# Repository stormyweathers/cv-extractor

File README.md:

# CV Extractor

This is an envelope detector eurorack module.
It is intended to take in eurorack signals or audio input and output the envelope.

## Description of schematic
An input waveform passes through an adjustable gain noninverting amplifier, then an active rectifier, then finally a 2-pole sallen-key LPF with adjustable gain and cutoff.

## Features

    * Buffered input/output
    * Adjustable input/output gain
    * Adjustable timescale of envelope detection

## Rack info

    * +12V: ?? mA
    * -12V: ?? mA
    *  +5V: unused
    * Width: 8HP   

## Issues

The module works, but its not that great.

    * Gain Pots are oriented reverse, unintuitive
    * Turning the cutoff knob can cause it to oscillate
    * The gain range is too large

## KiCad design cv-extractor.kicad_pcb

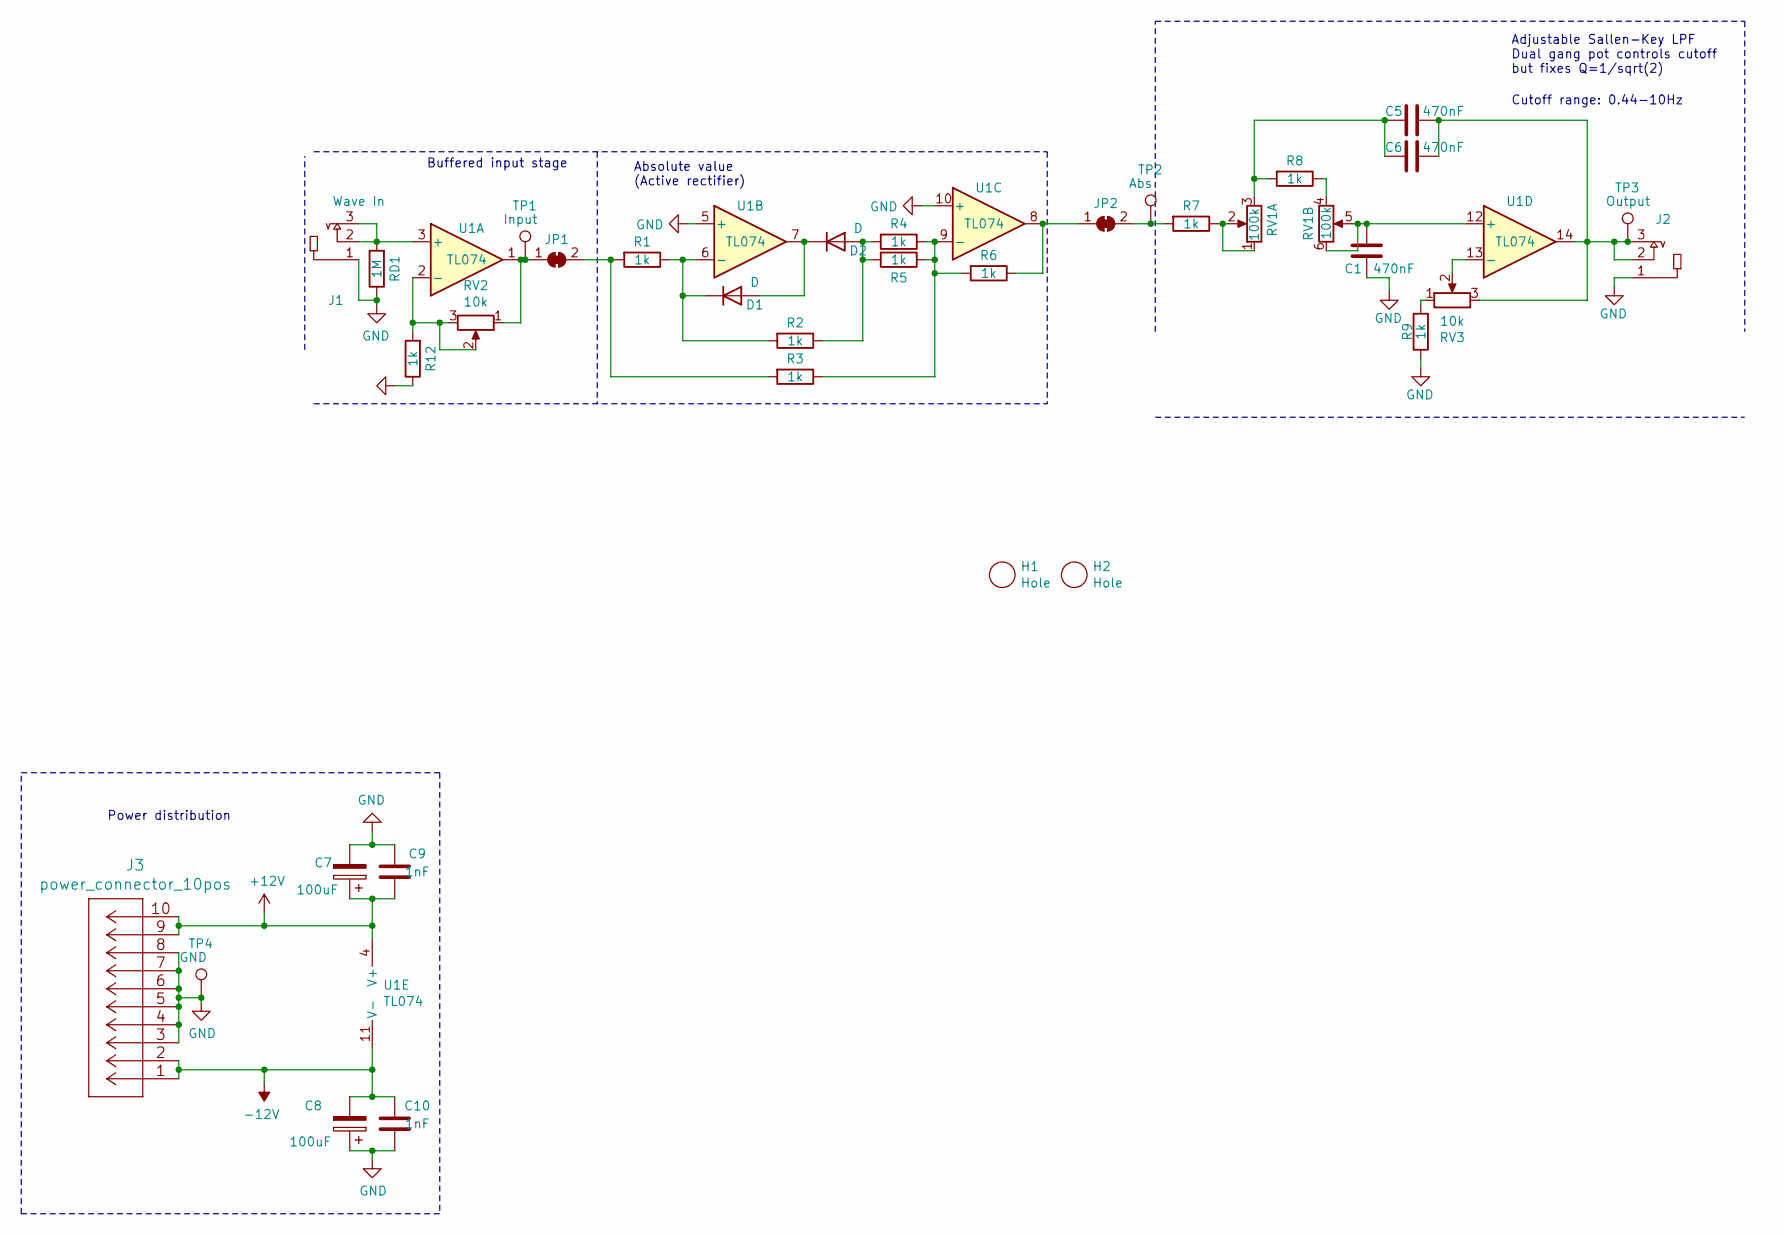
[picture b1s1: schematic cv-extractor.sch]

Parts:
C1, C5, C6: 470nF; C_0603_1608Metric; JLCPCB C1623
C7, C8: 100uF; CP_Elec_6.3x7.7; JLCPCB C176675
C9, C10: 1nF; C_0603_1608Metric; JLCPCB C1588
D1, D2: D; D_SOD-323F; JLCPCB C2128
H1, H2: Hole; MountingHole_3.2mm_M3
J1: Wave In; mono-jack-thonk
J2: CV Out; mono-jack-thonk
J3: power_connector_10pos; Digikey 732-2094-ND
JP1, JP2: SolderJumper_2_Bridged; SolderJumper-2_P1.3mm_Open_RoundedPad1.0x1.5mm
R1, R2, R3, R4, R5, R6, R7, R8, R9, R12: 1k; R_0603_1608Metric; JLCPCB C21190
RD1: 1M; R_0603_1608Metric; JLCPCB C21190
RV1: 100k; dual-pot-P120
RV2, RV3: 10k; pot_bourns_PTV09
TP1: Input; TestPoint_TP107
TP2: Abs; TestPoint_TP107
TP3: Output; TestPoint_TP107
TP4: GND; TestPoint_TP107
U1: TL074; SOIC-14_3.9x8.7mm_P1.27mm

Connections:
+12V: C7.1, C9.2, J3.9, J3.10, U1.4 (V+)
-12V: C8.2, C10.1, J3.1, J3.2, U1.11 (V-)
GND: C1.1, C7.2, C8.1, C9.1, C10.2, J1.1, J2.1, J3.3, J3.4, J3.5, J3.6, J3.7, J3.8, R9.1, R12.1, RD1.1, TP4.1, U1.5 (+), U1.10 (+)
unnamed: C1.2, RV1.5, RV1.6, U1.12 (+)
unnamed: C5.1, C6.1, R8.2, RV1.3
unnamed: C5.2, C6.2, J2.2, J2.3, RV3.3, TP3.1, U1.14
unnamed: D1.1 (K), R1.1, R2.2, U1.6 (-)
unnamed: D1.2 (A), D2.1 (K), U1.7
unnamed: D2.2 (A), R2.1, R4.2, R5.2
unnamed: J1.2, J1.3, RD1.2, U1.3 (+)
unnamed: JP1.1 (A), RV2.1, TP1.1, U1.1
unnamed: JP1.2 (B), R1.2, R3.2
unnamed: JP2.1 (A), R6.1, U1.8
unnamed: JP2.2 (B), R7.2, TP2.1
unnamed: R3.1, R4.1, R5.1, R6.2, U1.9 (-)
unnamed: R7.1, RV1.1, RV1.2
unnamed: R8.1, RV1.4
unnamed: R9.2, RV3.1
unnamed: R12.2, RV2.2, RV2.3, U1.2 (-)
unnamed: RV3.2, U1.13 (-)

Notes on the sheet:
Adjustable Sallen-Key LPF Dual gang pot controls cutoff but fixes Q=1/sqrt(2)
Buffered input stage
Power distribution
Absolute value (Active rectifier)
Cutoff range: 0.44-10Hz

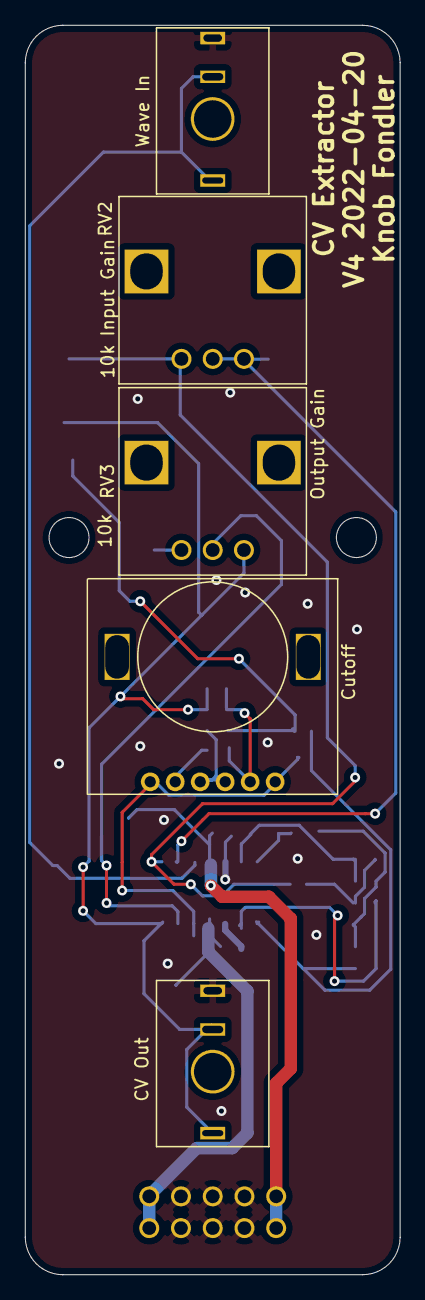
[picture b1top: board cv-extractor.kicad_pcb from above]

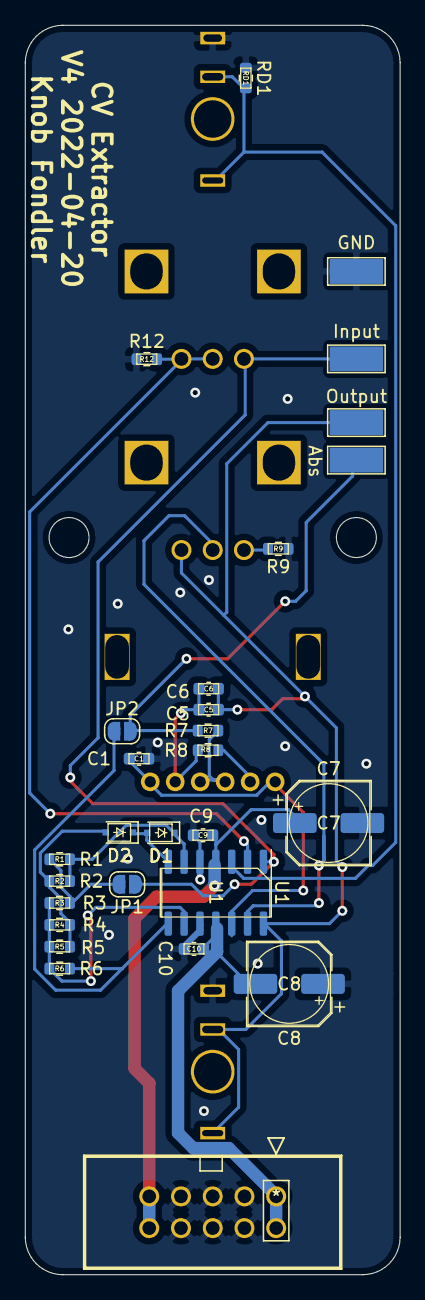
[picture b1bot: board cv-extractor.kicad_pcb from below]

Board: 2 copper layers, 30.0 x 100.0 mm, 35 parts (28 on the bottom side), 20 nets.

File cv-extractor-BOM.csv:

Comment,Designator,Footprint,Quantity
100uF,"C3,C1,C2,C4,C5,C6",C_1206_3216Metric,6
100uF,"C7,C8",CP_Elec_6.3x7.7,2
1nF,"C9,C10",C_0603_1608Metric,2
D,"D1,D2",D_SMA,2
1k,"R1,R2,R3,R4,R5,R6,R7,R8",R_0603_1608Metric,8
TL074,U1,SOIC-14_3.9x8.7mm_P1.27mm,1

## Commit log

2021-10-25 init commit v1
2021-10-27 narrower profile, added test points, reduced cutoff range, V2 for fab
2024-04-02 havent been good about commits, its at V4 now
2024-04-02 added readme

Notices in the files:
parts and their libraries:
Copyright 2016 Accelerated Designs. All rights reserved.
